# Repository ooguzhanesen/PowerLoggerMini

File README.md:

# Mini Power Logger

> **Hazırlayan:** Oğuzhan ESEN  
> **Proje Adı:** Mini Power Logger
> **Tarih:** 11 Kasım 2025
> **Versiyon:** v1.0
---

## İçindekiler

---

## 1. Giriş

Mini Power Logger, gerilim, akım ve güç tüketimini ölçmek, bu verileri hafızaya kaydetmek ve ekran üzerinden anlık olarak göstermek amacıyla geliştirilmiş bir izleme kartıdır.

Sistem, STM32F103 mikrodenetleyici tabanlıdır ve INA228 yüksek çözünürlüklü akım–voltaj sensörü sayesinde 20 bit çözünürlükte hassas ölçüm yapabilmektedir. Ayrıca  ölçülen veriler microSD karta kaydedebilmekte ve aynı zamanda OLED ekranda anlık değerler görülebilmektedir.

Mini Power Logger, arge projelerinde üzeritilen prototip ve cihazların güç tüketimini incelemek amacıyla tasarlanmıştır.

---

## 2. Tasarımın Amacı ve Kapsamı

Bu tasarımın temel amacı, enerji tüketimini düşük maliyetle, taşınabilir bir sistem üzerinden izleyebilmek ve ölçüm sonuçlarını kolayca kayıt altına almaktır.
Mini Power Logger, aşağıdaki fonksiyonları yerine getirir:

* 7–28 V DC aralığında güç girişi

* INA228 sensörü ile akım ve voltaj ölçümü (3 A'e kadar)

* microSD kart üzerinden veri kaydı

* 0.96” OLED ekran ile anlık ölçüm gösterimi

* USB Type-C bağlantısı (alternatif besleme ve veri aktarımı)

* 2 adet sıcaklık sensörü (cihazın çeşitli konumlarında sıcaklık ölçümü alabilmek için)

* 3 adet buton (menü kontrolü ve fonksiyon seçimi)

* Buzzer ile sesli uyarı

---

## 3. Sistem Blok Diyagramı

---

## 4. Şematik ve PCB
[Şematik tasarım için tıklayın.](docs/mini_power_logger.pdf)

---

## 5. Test Notları

---

## 6. Geliştirme ve İyileştirme Önerileri

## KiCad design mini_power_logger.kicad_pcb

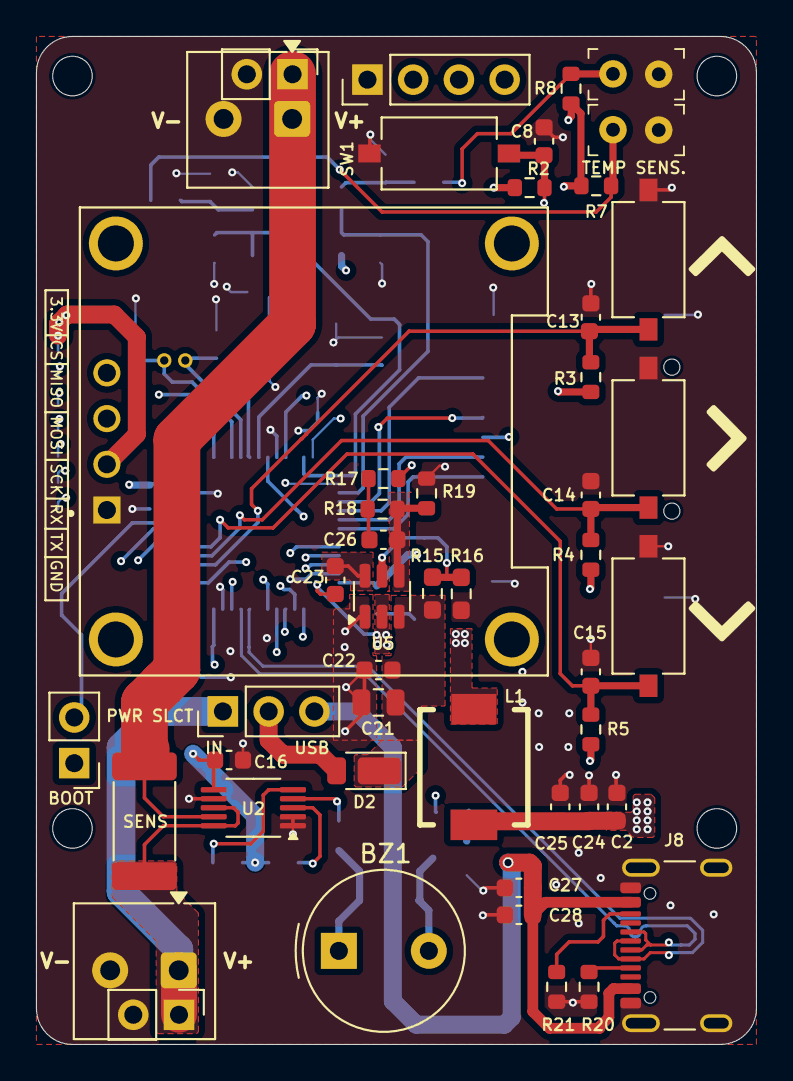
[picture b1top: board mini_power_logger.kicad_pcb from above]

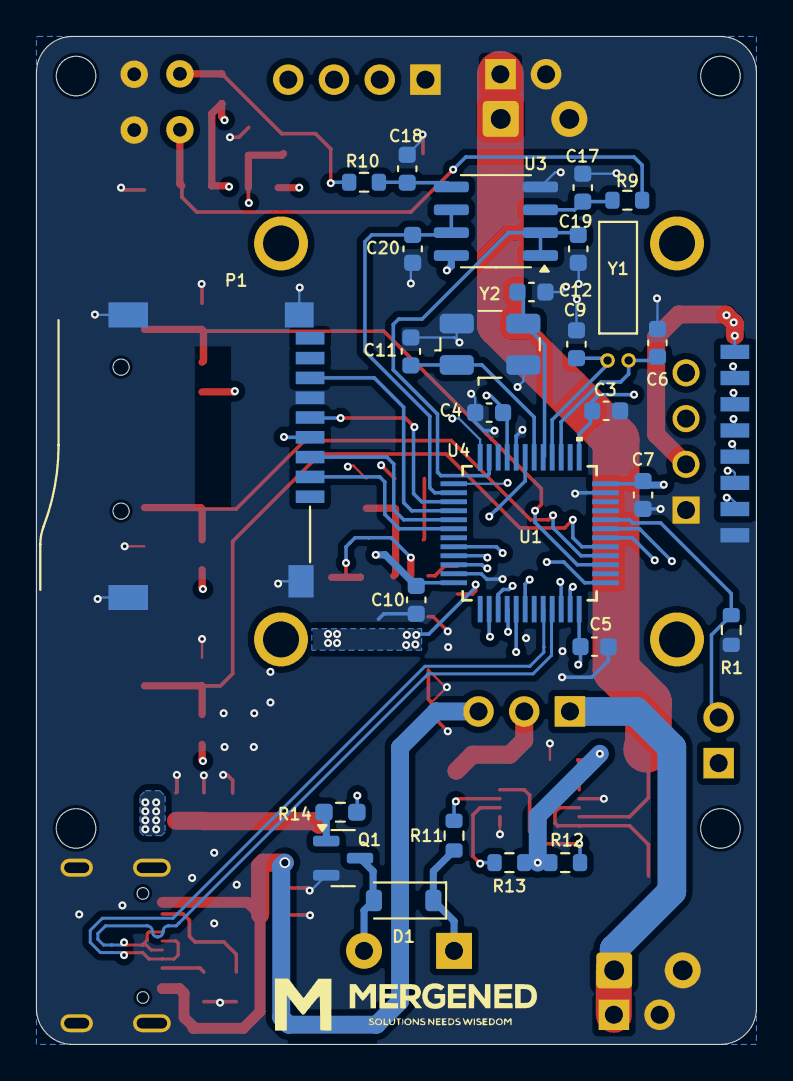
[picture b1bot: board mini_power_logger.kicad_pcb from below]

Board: 4 copper layers, 40.0 x 56.0 mm, 76 parts (28 on the bottom side), 51 nets.

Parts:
BZ1: Buzzer; Buzzer_TDK_PS1240P02BT_D12.2mm_H6.5mm
C1: Connector_PinHeader_2.54mm; PinHeader_1x08_P2.54mm_Vertical_SMD_Pin1Right
C2: 4.7uF; C_0603_1608Metric
C3, C4, C5, C7, C8, C10, C13, C14, C15, C22, C23, C27, C28: 100nF; C_0603_1608Metric
C6, C9: 8pF; C_0603_1608Metric
C11, C12: 27pF; C_0603_1608Metric
C16: 100nf; C_0603_1608Metric
C17, C18, C19, C20: 10nF; C_0603_1608Metric
C21: 10uF; C_0805_2012Metric
C24, C25: 22uF; C_0603_1608Metric
C26: 47pF; C_0603_1608Metric
D1: MBR0540; D_SOD-123
D2: SBR3U40P1-7; D_PowerDI-123
J1, J1#2: 691322310002; PinHeader_1x02_P2.54mm_Vertical
J1#3: Screw_Terminal_01x03; PinHeader_1x03_P2.54mm_Vertical
J2, J3: Screw_Terminal_01x02; TerminalBlock_Phoenix_MKDS-1-2-3.81_1x02_P3.81mm_Horizontal
J4: Conn_01x04_Pin; PinHeader_1x04_P2.54mm_Vertical
J5: Conn_01x02_Pin; PinHeader_1x02_P2.54mm_Vertical
J6, J7: 10k NTC Connector; PinHeader_1x2_P2.54mm
J8: USB_C_Receptacle_USB2.0; USB_C_Receptacle_GCT_USB4105-xx-A_16P_TopMnt_Horizontal
L1: 6.8uH; INDC6060X300
P1: ST-TF-003A, L-KLS1-TF-003; sdcardsoket
Q1: BC817-40-HT; SOT-23
R1, R2, R3, R4, R5, R7, R8, R11, R12, R13: 10k; R_0603_1608Metric
R6: SHUNT; R_2512_6332Metric_Pad1.40x3.35mm_HandSolder
R9, R10: 1k; R_0603_1608Metric
R14: 1K; R_0603_1608Metric_Pad0.98x0.95mm_HandSolder
R15: 511k; R_0603_1608Metric_Pad0.98x0.95mm_HandSolder
R16: 105k; R_0603_1608Metric_Pad0.98x0.95mm_HandSolder
R17: 49.9; R_0603_1608Metric
R18: 100K; R_0603_1608Metric
R19: 22.1k; R_0603_1608Metric
R20, R21: 5.1k; R_0603_1608Metric
SW1, SW2, SW3, SW4: SW_Push; SW_Tactile_SPST_NO_Straight_CK_PTS636Sx25SMTRLFS
U1: STM32F103C8T6; LQFP48_STM
U2: INA228; VSSOP-10_3x3mm_P0.5mm
U3: OPA2197xD; SOIC-8_3.9x4.9mm_P1.27mm
U4: DM-OLED096-636; MODULE_DM-OLED096-636
U5: TPS54302; SOT-23-6
Y1: AB26T-32.768KHZ-6; XTAL_AB26T-32.768KHZ-6
Y2: XD8M000000S418; Crystal_SMD_EuroQuartz_MJ-4Pin_5.0x3.2mm

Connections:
+3.3V: BZ1.1 (+), C1.1, C2.1, C3.1, C4.1, C5.1, C7.1, C10.1, C16.2, C24.2, C25.2, D1.1 (K), J4.2, J5.1, L1.2, P1.4 (VDD), R2.1, R3.1, R4.1, R5.1, R7.2, R8.2, R11.1, R12.1, R13.1, R17.1, U1.1 (VBAT), U1.9 (VDDA), U1.24 (VDD), U1.36 (VDD), U1.48 (VDD), U2.6 (VS), U3.8 (V+), U4.2 (VCC_IN)
/BUZZER_PIN: R14.1, U1.30 (PA9)
/Power/POWER_IN_P: D2.2 (A), J1#3.2
/SD Card & Oled Screen/OLED_SCL: U1.42 (PB6), U4.3 (SCL)
/SD Card & Oled Screen/OLED_SDA: U1.43 (PB7), U4.4 (SDA)
/SD Card & Oled Screen/SD_CS: P1.2 (DAT3), U1.18 (PB0)
/SD Card & Oled Screen/SD_MISO: P1.7 (DAT0), U1.16 (PA6)
/SD Card & Oled Screen/SD_MOSI: P1.3 (CMD), U1.17 (PA7)
/SD Card & Oled Screen/SD_SCK: P1.5 (CLK), U1.15 (PA5)
/SHUNT_V+: J1.1, J1#3.1, J3.1, R6.1, U2.8 (Vbus), U2.10 (Vin+)
/SHUNT_V-: J1#2.1, J2.1, R6.2, U2.9 (Vin-)
/SPI2_CS: C1.2, U1.29 (PA8)
/SPI2_MISO: C1.3, U1.27 (PB14)
/SPI2_MOSI: C1.4, U1.28 (PB15)
/SPI2_SCK: C1.5, U1.26 (PB13)
/Temp. & Power Sensors/ADC_TEMP1: C19.1, U1.11 (PA1), U3.1, U3.2 (-)
/Temp. & Power Sensors/ADC_TEMP2: C20.1, U1.14 (PA4), U3.6 (-), U3.7
/Temp. & Power Sensors/ALERT: R13.2, U1.20 (PB2), U2.3 (~Alert)
/Temp. & Power Sensors/SCL: R12.2, U1.21 (PB10), U2.5 (SCL)
/Temp. & Power Sensors/SDA: R11.2, U1.22 (PB11), U2.4 (SDA)
/Type C Connector/CC1: J8.A5 (CC1), R20.1
/Type C Connector/CC2: J8.B5 (CC2), R21.1
/Type C Connector/USB2_N: J8.A7 (D-), J8.B7 (D-), U1.32 (PA11)
/Type C Connector/USB2_P: J8.A6 (D+), J8.B6 (D+), U1.33 (PA12)
/UART2_RX: C1.6, U1.13 (PA3)
/UART2_TX: C1.7, U1.12 (PA2)
/USB_PWR: C27.1, C28.1, J1#3.3, J8.A4 (VBUS), J8.A9 (VBUS), J8.B4 (VBUS), J8.B9 (VBUS)
/stm32f103/BUTTON_1: C13.1, R3.2, SW2.2, U1.39 (PB3)
/stm32f103/BUTTON_2: C14.1, R4.2, SW3.2, U1.40 (PB4)
/stm32f103/BUTTON_3: C15.1, R5.2, SW4.2, U1.41 (PB5)
/stm32f103/CLK: J4.4, U1.37 (PA14)
/stm32f103/DIO: J4.3, U1.34 (PA13)
GND: C1.8, C2.2, C3.2, C4.2, C5.2, C6.2, C7.2, C8.2, C9.2, C10.2, C11.2, C12.2, C13.2, C14.2, C15.2, C16.1, C17.2, C18.2, C19.2, C20.2, C21.2, C22.2, C24.1, C25.1, C27.2, C28.2, J1.2, J1#2.2, J2.2, J3.2, J4.1, J6.1, J7.1, J8.A1 (GND), J8.A12 (GND), J8.B1 (GND), J8.B12 (GND), J8.S1 (SHIELD), P1.6 (VSS), P1.G1 (GND), P1.G2 (GND), P1.G3 (GND), P1.G4 (GND), Q1.2 (E), R1.2, R16.2, R19.2, R20.2, R21.2, SW1.1, SW2.1, SW3.1, SW4.1, U1.8 (VSSA), U1.23 (VSS), U1.35 (VSS), U1.47 (VSS), U2.1 (A1), U2.2 (A0), U2.7 (GND), U3.4 (V-), U4.1 (GND), U5.1 (GND), Y2.2, Y2.4
unnamed: BZ1.2 (-), D1.2 (A), Q1.3 (C)
unnamed: C26.2, R17.2, R18.1
unnamed: C21.1, C22.1, D2.1 (K), R15.1, U5.3 (VIN)
unnamed: J5.2, R1.1, U1.44 (BOOT0)
unnamed: J6.2, R7.1, R9.1
unnamed: J7.2, R8.1, R10.1
unnamed: Q1.1 (B), R14.2
unnamed: C8.1, R2.2, SW1.2, U1.7 (NRST)
unnamed: C6.1, U1.3 (PC14-OSC32_IN), Y1.1
unnamed: C9.1, U1.4 (PC15-OSC32_OUT), Y1.2
unnamed: C12.1, U1.5 (PD0_OSC_IN), Y2.3
unnamed: C11.1, U1.6 (PD1_OSC_OUT), Y2.1
unnamed: C17.1, R9.2, U3.3 (+)
unnamed: C18.1, R10.2, U3.5 (+)
unnamed: C23.1, U5.6 (BOOT)
unnamed: R15.2, R16.1, U5.5 (EN)
unnamed: C26.1, R18.2, R19.1, U5.4 (FB)
unnamed: C23.2, L1.1, U5.2 (SW)

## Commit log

2025-11-18 final porject.
2025-12-18 final design.
2025-12-18 final project
